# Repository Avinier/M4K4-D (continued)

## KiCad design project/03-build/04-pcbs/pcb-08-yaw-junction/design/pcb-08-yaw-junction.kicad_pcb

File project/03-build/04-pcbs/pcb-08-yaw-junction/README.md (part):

# PCB-08 — Yaw junction

Stationary end of the clock spring: body-side power and signal connectors to the cassette FFCs (`J8-6`, `J8-7`).

**[D-093](../../decisions.md#d-093) scope (2026-11-06).** PCB-02 and PCB-03 are bought modules now, so the `W23a` (`J8-3`) and `W23b` (`J8-5`) permit and status cables and the D-082 `ARM_REQ` conductor are gone. PCB-08 **gains the yaw servo plug** that was PCB-03 `J3-5`: Feetech 5264-3P, 1 GND, 2 `+11V1_YAW` (from the bought yaw buck-boost, 11.1 V), 3 `SERVO_DATA` (from C2 through W43). It keeps `J8-1` (head power from the bought modules), `J8-4` (RS-422 head link, J9-1 order per D-092) and the `J8-6`/`J8-7` cassette FFCs. Reassign the freed W43 conductors at design.

| | |
|---|---|
| Register | [04-pcbs board register](../README.md#board-register) |
| Project BOM | CH-083 in [BOM.csv](../../BOM.csv) |
| Location | Body, under the yaw adapter plate |
| Specification | [05-harness](../../05-harness/README.md)<br>[D-039](../../decisions.md#d-039), [D-044](../../decisions.md#d-044) |
| CAD placeholder | `_yaw_junction_board()` in [`body_v1_model.py`](../../02-body/v1/cad/body_v1_model.py) |
| CAD labels | `YAW_JUNCTION_PCB08` |
| Final CAD | `Custom PCBs › PCB-08 yaw junction` in [makad-v1.step.py](../../final/v1/cad/makad-v1.step.py) |

## Stages

See [workflow.md](../workflow.md) for what each stage involves and when it is done.

| Stage | Status | Revision / evidence | Date |
|---|---|---|---|
| 1. Design | **Rev A draft complete**: routed, populated fit 18/18, fold predicted 10/10, [fab/revA](fab/revA/README.md) written (**do not order**) | [design/](design/): Nightly ERC 0/0, netlist audit 14/14 on 51 pins, parity DRC 0 violations / 0 unconnected / 0 parity; [STEP](cad/pcb-08-yaw-junction-revA.step) with detailed connector models | 2026-11-09 |
| 2. Procure | Waits for the PCB-12/14 designs (D-064) and the bench gates in [fab/revA](fab/revA/README.md#before-ordering) | Do not order fab/revA yet | — |
| 3. Integrate | Rev A STEP installed in final CAD (`pcb_integration.py`, integration PASS) | Physical acceptance open | 2026-11-10 |

## Design inputs (2026-11-09; preliminary)

The board is a passive stator junction: it distributes three head power/return pairs from `J8-1` to `J8-6`, passes the two RS-422 pairs from `J8-4` through `J8-7`, brings `SERVO_DATA` back from `J8-7` to the body-fixed yaw `J8-8`, and takes the yaw rail/return from `W17` pads to `J8-8`. There is no `ARM_REQ`, permit chain, or old `J8-3`/`J8-5` header. No 11.1 V yaw power goes onto either FFC. See [D-093](../../decisions.md#d-093), [D-092](../../decisions.md#d-092), the [harness pinouts](../../05-harness/README.md#5-pinouts-and-polarity), and the [servo link contract](../feetech-link-contract.md).

| Interface | Fixed electrical contract | Board action |
|---|---|---|
| `J8-1`, Micro-Fit 3.0 2×3, right-angle, mating −X | 1 `+6V3_HEAD_PR` (D-100), 2 `+5V_C2`, 3 `+5V_DISPLAY`, 4 `GND_HEAD`, 5 `GND_C2`, 6 `GND_DISPLAY` | Preserve the three supply/return pairs; do not use a signal return as a power-current shortcut |
| `J8-4`, GH6 | 1 GND, 2 `C0TX+`, 3 `C0TX−`, 4 `C2TX−`, 5 `C2TX+`, 6 spare | Pass both differential pairs to `J8-7` in the same polarity. Keep pin 6 isolated unless a later interface decision assigns it |
| `J8-6`, 22-way power FFC | Pitch/roll 7 positive + 7 return; C2 2 + 2; display 2 + 2 | A conductor may carry no more than its connector and cable rating; pair the same rail only at the board ends |
| `J8-7`, 22-way sideband FFC | RS-422 pairs, signal reference and `SERVO_DATA`; former permit/status nets removed | Allocate explicit grounds beside signal groups; leave unused contacts unconnected and labelled, never silently repurpose them as power |
| `W17` → `J8-8`, yaw servo | `J8-8`: 1 GND, 2 `+11V1_YAW`, 3 `SERVO_DATA` | W17 enters on rated pads/strain relief; check the received servo cable by cavity number before energizing |

**FFC maps ([D-100](../../decisions.md#d-100), pending cable orientation).** Number by the *connector's marked contact number* at PCB-08, then measure whether each cable arrives straight or mirrored at PCB-14. PCB-14 remains 1:1; its physical orientation must not reverse these names. `J8-6`: 1–7 `+6V3_HEAD_PR`, 8–14 `GND_HEAD`, 15–16 `+5V_C2`, 17–18 `GND_C2`, 19–20 `+5V_DISPLAY`, 21–22 `GND_DISPLAY`. `J8-7` is **signal-only**: 1 GND reference, 2 `C0TX+`, 3 `C0TX−`, 4 GND reference, 5 `C2TX−`, 6 `C2TX+`, 7 GND reference, 8 `SERVO_DATA`, 9 GND reference, 10–22 isolated and labelled. The 13/13 option (10–15 `GND_HEAD`, 16–21 head positive on `J8-7`) is the recorded fallback only if the measured FFC or N2 fails the 7/7 map. The GND reference source and head-end return must be resolved with PCB-12; the separate `J8-1` returns must not be unintentionally joined on the stator.

**Signal ground (builder, 2026-11-09; [D-100](../../decisions.md#d-100) amendment).** PCB-08 has one signal ground net, **`GND_SIG`**: `J8-4` pin 1 (C0 link GND over W24), `J8-7` pins 1/4/7/9, and `J8-8` pin 1 with the W17 yaw return. `SERVO_DATA` is a single-ended 1 Mbps half-duplex line from C2 to the yaw servo, so its return must run beside it on the `J8-7` references and meet the servo's own ground at `J8-8`. `GND_HEAD` (`J8-1` pin 4 → `J8-6` 8–14), `GND_C2` and `GND_DISPLAY` stay separate on PCB-08, each paired with its supply back to the star. PCB-12 bonds `GND_SIG` to C2 logic ground near the RS-422 receiver and servo-bus driver; all head grounds join there. **Accepted loop:** Pi → M4 → star → M3 → W17 → PCB-08 → W24 → PCB-09 → Pi. Most yaw stall current returns directly on W17, but some can share the W24 GND (GH, 1 A contacts); RS-422 is differential. **Bench:** W24 GND current at yaw stall, C0↔C2 common-mode voltage under simultaneous servo/display load, and `SERVO_DATA` edges at `J8-8`. **Fallback:** a series ferrite or low-value resistor between `J8-4` pin 1 and `GND_SIG` (leave a footprint at layout).

**Current and voltage-drop screen (`E`, not a measured cable).** FH34SRJ is rated 0.5 A/contact. Seven equal-sharing contacts have a nominal 3.5 A sum against the 2.8 A head allowance; two have 1.0 A for each C2/display branch. For voltage, assume copper resistivity 0.01724 Ω·mm²/m, conductor width 0.3 mm, total FFC length 0.3 m, four ZIF contact interfaces in series, and the FH34SRJ specification's 0.1 Ω maximum per contact **including 8 mm of FFC bulk**. Adding that limit to the full cable length double-counts a small portion, so it is deliberately conservative. The table is reproduced by [`head_power_drop.py`](head_power_drop.py). It shows a 0.035 mm conductor and a thinner 0.027 mm sensitivity case. The latter matches the nominal copper thickness in Raspberry Pi's **standard-mini display cable drawing**, but neither case is a claim about the actual BO-050 mini-mini or power FFC. [FH34SRJ specification](https://www.hirose.com/en/product/p/CL0580-1254-3-99); [Raspberry Pi cable drawing](https://pip-assets.raspberrypi.com/categories/903-flexible-printed-circuit-fpc-cable-for-display-and-camera/documents/RP-008145-DS-1-mini-display-cable-200mm-reference-drawing.pdf).

| Copper thickness | Head positive/return conductors | Calculated loop Ω | Drop at 2.8 A | Terminal at 5.5 V | Terminal at 6.0 V | Terminal at 6.3 V |
|---:|---:|---:|---:|---:|---:|---:|
| 0.035 mm | 7 / 7 | 0.255 | 0.714 V | 4.79 V | 5.29 V | 5.59 V |
| 0.027 mm | 7 / 7 | 0.297 | 0.831 V | 4.67 V | 5.17 V | 5.47 V |
| 0.035 mm | 13 / 13 | 0.137 | 0.384 V | 5.12 V | 5.62 V | 5.92 V |
| 0.027 mm | 13 / 13 | 0.160 | 0.447 V | 5.05 V | 5.55 V | 5.85 V |

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
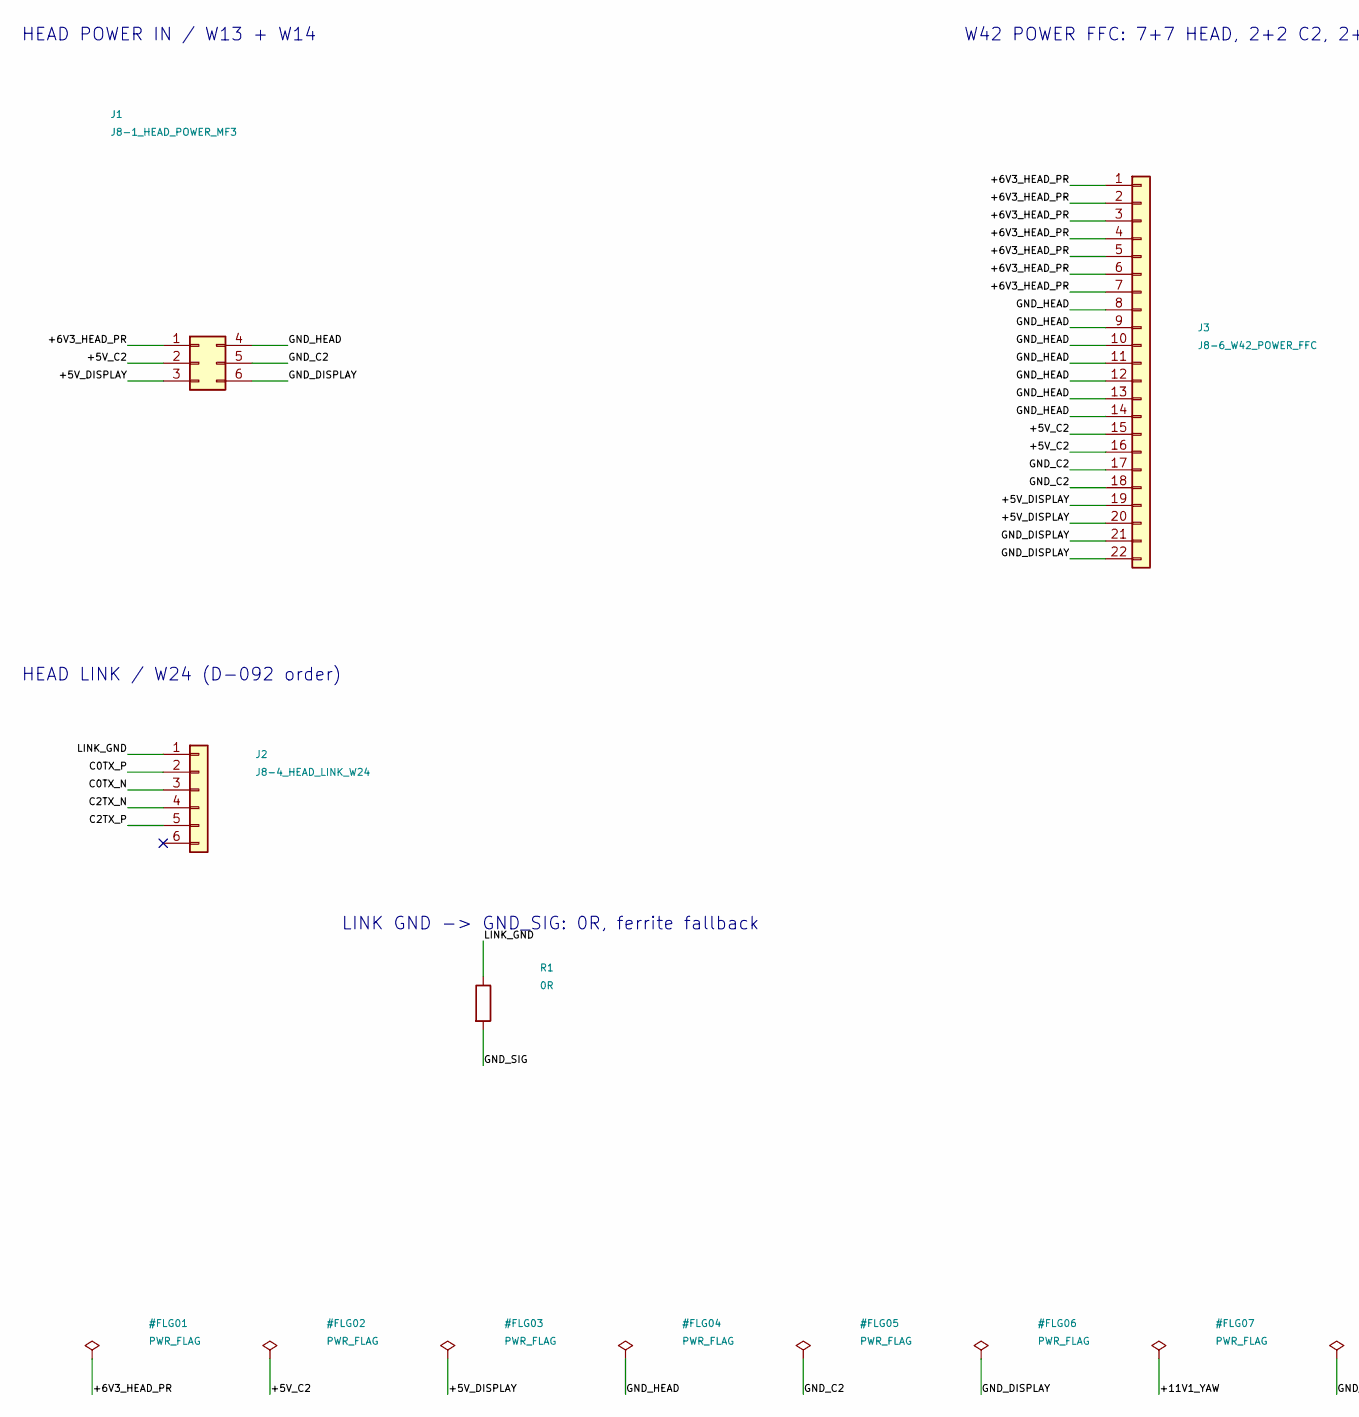
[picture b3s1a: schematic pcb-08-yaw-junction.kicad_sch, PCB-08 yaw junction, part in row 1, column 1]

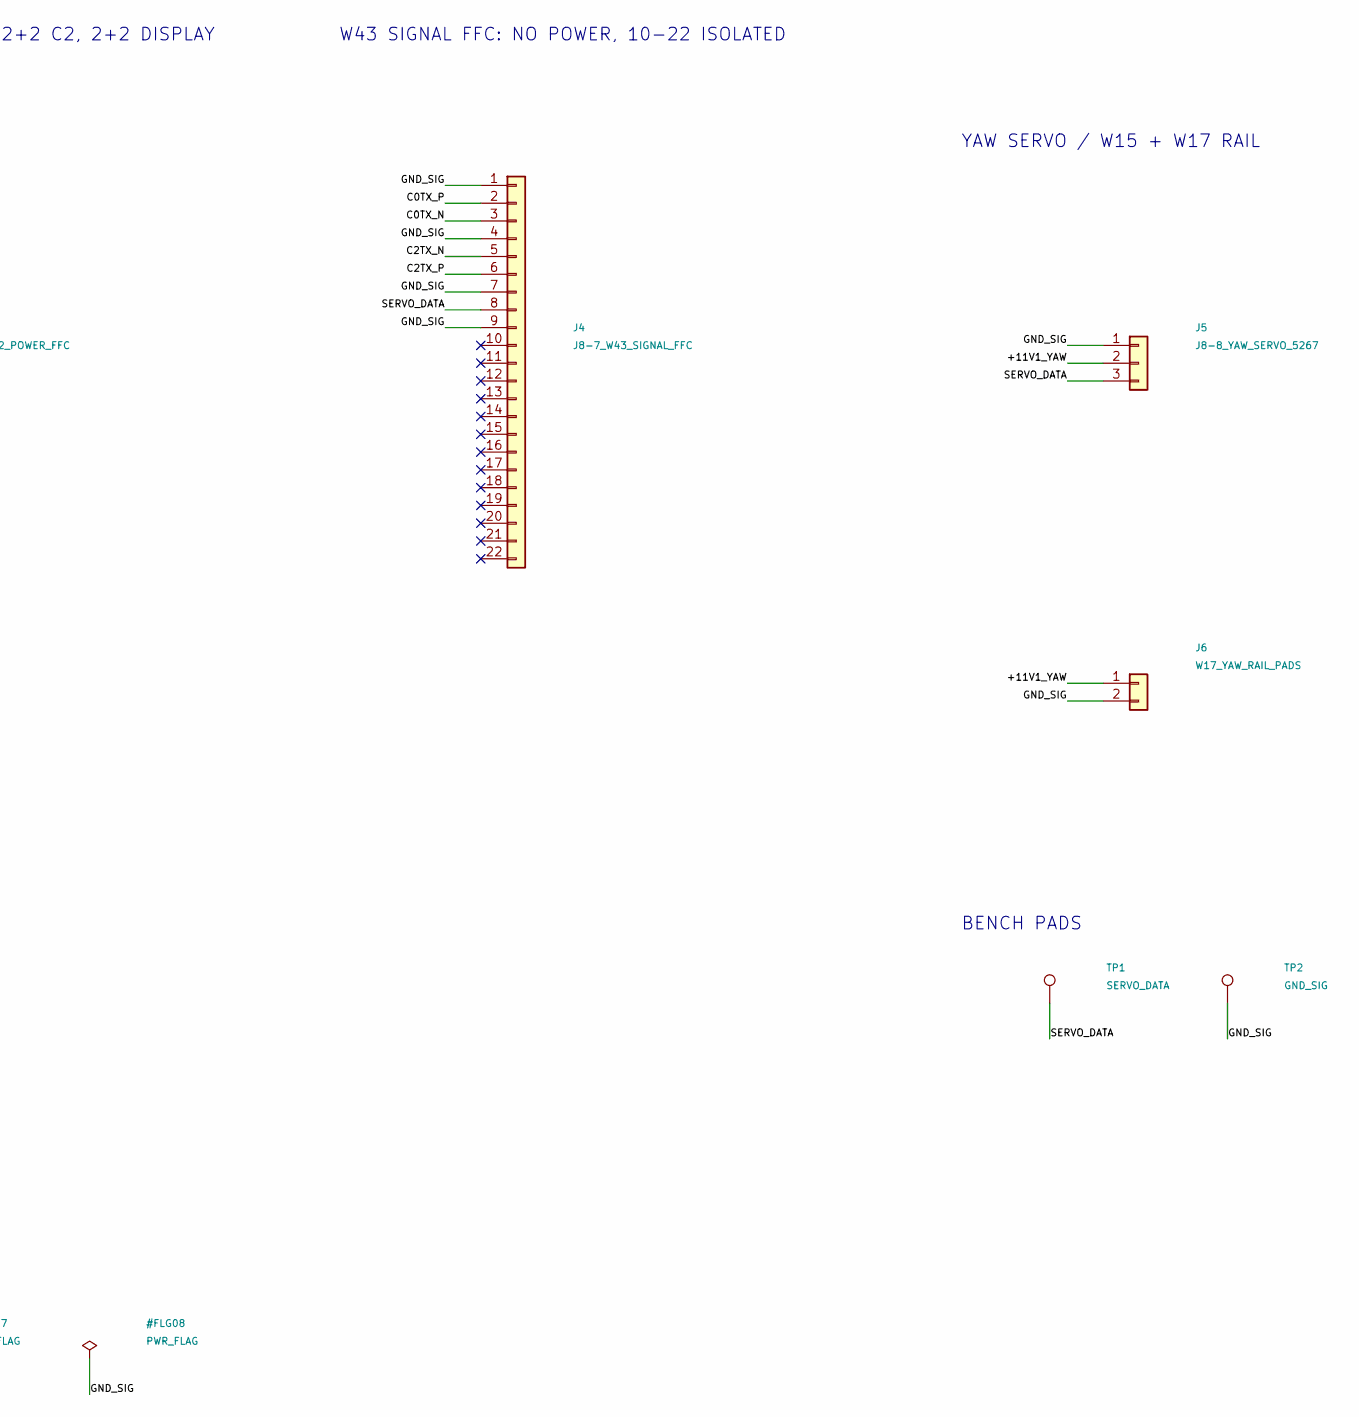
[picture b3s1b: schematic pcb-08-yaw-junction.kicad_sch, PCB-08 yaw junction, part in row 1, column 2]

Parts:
J1: J8-1_HEAD_POWER_MF3; Molex_Micro-Fit_3.0_43045-0621_2x03-1MP_P3.00mm_Horizontal
J2: J8-4_HEAD_LINK_W24; JST_GH_BM06B-GHS-TBT_1x06-1MP_P1.25mm_Vertical
J3: J8-6_W42_POWER_FFC; Hirose_FH34SRJ-22S-0.5SH_1x22_P0.50mm
J4: J8-7_W43_SIGNAL_FFC; Hirose_FH34SRJ-22S-0.5SH_1x22_P0.50mm
J5: J8-8_YAW_SERVO_5267; Molex_SPOX_5267-03A_1x03_P2.50mm_Vertical
J6: W17_YAW_RAIL_PADS; SolderWire-0.5sqmm_1x02_P4.6mm_D0.9mm_OD2.1mm
R1: 0R; R_0805_2012Metric
TP1: SERVO_DATA; TestPoint_Pad_D1.0mm
TP2: GND_SIG; TestPoint_Pad_D1.0mm

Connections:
/+5V_C2: J1.2, J3.15, J3.16
/+5V_DISPLAY: J1.3, J3.19, J3.20
/+6V3_HEAD_PR: J1.1, J3.1, J3.2, J3.3, J3.4, J3.5, J3.6, J3.7
/+11V1_YAW: J5.2, J6.1
/C0TX_N: J2.3, J4.3
/C0TX_P: J2.2, J4.2
/C2TX_N: J2.4, J4.5
/C2TX_P: J2.5, J4.6
/GND_C2: J1.5, J3.17, J3.18
/GND_DISPLAY: J1.6, J3.21, J3.22
/GND_HEAD: J1.4, J3.8, J3.9, J3.10, J3.11, J3.12, J3.13, J3.14
/GND_SIG: J4.1, J4.4, J4.7, J4.9, J5.1, J6.2, R1.2, TP2.1 (1_1)
/LINK_GND: J2.1, R1.1
/SERVO_DATA: J4.8, J5.3, TP1.1 (1_1)

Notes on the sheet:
HEAD POWER IN / W13 + W14
HEAD LINK / W24 (D-092 order)
LINK GND -> GND_SIG: 0R, ferrite fallback
W42 POWER FFC: 7+7 HEAD, 2+2 C2, 2+2 DISPLAY
W43 SIGNAL FFC: NO POWER, 10-22 ISOLATED
YAW SERVO / W15 + W17 RAIL
BENCH PADS

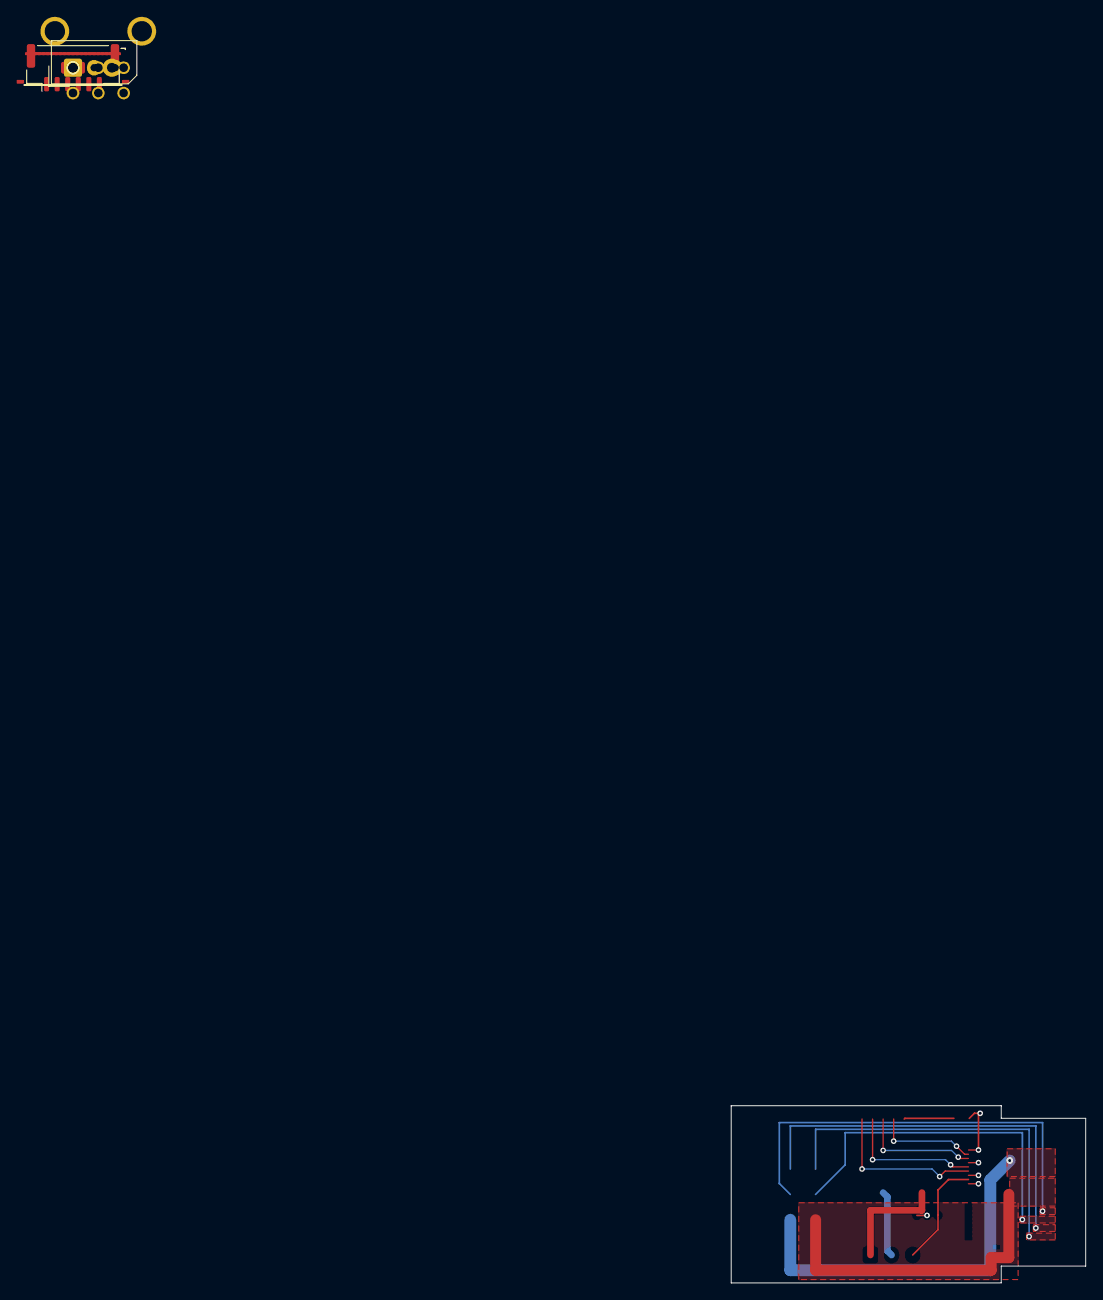
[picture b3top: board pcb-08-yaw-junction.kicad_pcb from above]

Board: 2 copper layers, 42.0 x 21.0 mm, 9 parts (0 on the bottom side), 14 nets.

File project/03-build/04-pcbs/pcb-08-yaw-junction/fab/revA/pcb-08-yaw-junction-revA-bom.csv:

"Comment","Designator","Footprint","Quantity","MPN","Manufacturer","LCSC Part #"
"J8-1_HEAD_POWER_MF3","J1","pcb08:Molex_Micro-Fit_3.0_43045-0621_2x03-1MP_P3.00mm_Horizontal","1","43045-0621","Molex",""
"J8-4_HEAD_LINK_W24","J2","Connector_JST:JST_GH_BM06B-GHS-TBT_1x06-1MP_P1.25mm_Vertical","1","BM06B-GHS-TBT(LF)(SN)(N)","JST",""
"J8-6_W42_POWER_FFC","J3","fh34:Hirose_FH34SRJ-22S-0.5SH_1x22_P0.50mm","1","FH34SRJ-22S-0.5SH(99)","Hirose",""
"J8-7_W43_SIGNAL_FFC","J4","fh34:Hirose_FH34SRJ-22S-0.5SH_1x22_P0.50mm","1","FH34SRJ-22S-0.5SH(99)","Hirose",""
"J8-8_YAW_SERVO_5267","J5","Connector_Molex:Molex_SPOX_5267-03A_1x03_P2.50mm_Vertical","1","22-03-5035 (5267-03A)","Molex",""
"0R","R1","Resistor_SMD:R_0805_2012Metric","1","RC0805JR-070RL","Yageo",""

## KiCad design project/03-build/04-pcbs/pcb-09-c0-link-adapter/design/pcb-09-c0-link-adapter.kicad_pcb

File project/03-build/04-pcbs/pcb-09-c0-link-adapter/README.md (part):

# PCB-09 — C0 link adapter

Pi-header board: 2 × RS-422 (THVD1451), audio pass-through and the enclosure-fan switch `J9-4`. **Rev A designed** ([D-092](../../decisions.md#d-092)): 77 × 22.7 × 1.6 mm, four layers, on the Pi header through a Samtec SSW-120-01-T-D socket and two M2.5 × 11 mm standoffs. **Rev B routed and CAD fitted on `pcb-09-revB`, not released** ([D-098](../../decisions.md#d-098)): 89 × 22.7 × 1.6 mm overall, adding the D-096 button/OFF and INA226 service interface. The #2813, Pi-image and populated bench gates below still apply; do not order either revision yet.

| | |
|---|---|
| Register | [04-pcbs board register](../README.md#board-register) |
| Project BOM | CH-084 in [BOM.csv](../../BOM.csv) |
| Location | Body, on the Pi header |
| Specification | [audiosystem.md §4](../../02-body/v1/research/audiosystem.md#4-audio-functions-on-the-shared-boards)<br>[D-042](../../decisions.md#d-042), [D-073](../../decisions.md#d-073), [D-074](../../decisions.md#d-074), [D-092](../../decisions.md#d-092), [D-098](../../decisions.md#d-098) |
| CAD placeholder | `_c0_link_adapter()` in [`body_v1_model.py`](../../02-body/v1/cad/body_v1_model.py) |
| CAD labels | `C0_LINK_ADAPTER_PCB09` |
| Final CAD | `Custom PCBs › PCB-09 C0 link adapter` in [makad-v1.step.py](../../final/v1/cad/makad-v1.step.py): rev-B KiCad STEP, standoffs, screws and five mated plugs ([pcb_integration.py](../../final/v1/cad/pcb_integration.py)); rev-B fit 8/8, mount 7/7 and integration PASS |

## Stages

See [workflow.md](../workflow.md) for what each stage involves and when it is done.

| Stage | Status | Revision / evidence | Date |
|---|---|---|---|
| 1. Design | **Rev B routed and CAD fitted; electrical release gates open** ([D-098](../../decisions.md#d-098)) | ERC 0; exported netlist audit PASS for 118 connected pins; Nightly DRC 0 violations / 0 unconnected / 0 parity; rev-B fit 8/8, mount 7/7, final integration PASS. `fab/revB` is a draft output, not an order release. | 2026-11-08 |
| 2. Procure | Waits for rev B and the design batch ([D-064](../../decisions.md#d-064)) | Do not order fab/revA | — |
| 3. Integrate | Rev B CAD replacement complete; physical acceptance open | [pcb_integration.py](../../final/v1/cad/pcb_integration.py), `check_pcb_integration.py`; J6 lead route to rear bay passes a 3 mm CAD reserve with 0.2 mm margin. J6 must be mated before tray installation. | 2026-11-08 |

### Rev B input — D-098

Preserve the rev A functions, socket, mounting and existing connector pinouts. Add accessible service access to **GPIO12 / header 32** for the qualified 0–3.3 V button-sense signal and **GPIO13 / header 33** for the M1 OFF command. The [D-098 amendment](../../decisions.md#d-098) assigns the INA226 to a local `i2c-gpio` bus: draft SDA on GPIO16 / header 36 and SCL on GPIO26 / header 37, plus Pi 3.3 V and GND. Physical pins 3/5 keep their rev A I²C1 routes to TP1/TP2 only. TP5 and TP1/TP2 are 1 mm probe pads, not harness terminations.

Rev B selects J6 as a top-entry GH6 on the +X extension. CAD checks its mated plug, a 3 mm lead corridor toward the rear buffer, and pre-mated tray insertion; add strain relief and pull-test the lead on the populated build. Keep the M1 ON pack-voltage node off this board: GPIO12 receives only the output of the measured high-impedance interface, with no back-power path into an unpowered Pi. Check GPIO13's inactive state through Pi reset, boot and halt, and any M1-to-GPIO13 injection with Pi power absent, before connecting OFF. ERC/DRC, six-net continuity/no-short checks and N1 are release gates. D-096's separate electrical HOLD still applies.

### Rev B routing study — 2026-11-08

The [rev B schematic](design/pcb-09-c0-link-adapter.kicad_sch) adds J6 (GH6: **1 3V3, 2 SDA, 3 SCL, 4 GND, 5 BTN_SENSE, 6 PWR_OFF**), R7 10 kΩ button pull-up to Pi 3V3, R8 2.2 kΩ button series, C5 100 nF optional/DNP, R9 1 kΩ OFF series, R10 100 kΩ OFF pull-down, and R11/R12 4.7 kΩ pull-ups for the software I²C bus. GPIO12/13 terminate at header pins 32/33; draft SDA/SCL terminate at pins 36/37. The connector nets are on the 3.3 V side; pack voltage and load current are absent. The received #2813 measurements still gate final values and buffer choice.

| Header pin | Rev B schematic net | Destination | Layout status |
|---|---|---|---|
| 3 / GPIO2 | I2C1_SDA | TP1 only, unchanged from rev A | Rev A route retained in rev B |
| 5 / GPIO3 | I2C1_SCL | TP2 only, unchanged from rev A | Rev A route retained in rev B |
| 32 / GPIO12 | BTN_GPIO12 | R8 → BTN_SENSE at J6.5 | Routed in rev B; DRC 0/0/0 |
| 33 / GPIO13 | OFF_GPIO13 | R9 → PWR_OFF at J6.6 | Routed in rev B; DRC 0/0/0 |
| 36 / GPIO16 | I2C_GPIO_SDA | R11 pull-up and J6.2 | Routed in rev B; DRC 0/0/0 |
| 37 / GPIO26 | I2C_GPIO_SCL | R12 pull-up and J6.3 | Routed in rev B; DRC 0/0/0 |

The draft rev B allocation has **15 functional GPIO** (rev A's 11 plus GPIO12/13/16/26) and keeps GPIO2/3 reserved for I²C1 service pads. Layout and CAD fit validate GPIO16/26 and a top-entry GH6 at the +X extension; electrical acceptance is pending.

An exploratory GH6 placement needed an extension at the bay's +X edge: the existing F.Cu courtyards occupy the top of the original bay. A geometric core-only probe of world X 66…78, Y 22.5…39, Z 106.25…108.25 found no intersecting robot solid. That probe did **not** validate the mated plug, cable exit, insertion sweep, mount or full board. Growing the +Y edge instead intersected the existing J9-1 mated plug and its reserve.

The manually routed exploratory I²C1 board failed Nightly DRC: **29 violations, 2 unconnected and 0 parity** ([study report](design/revB-routing-study-drc.json)). The SDA F.Cu L path crossed LRCLK near header pin 35; the proposed layer change landed on the existing 5 V via. The SCL B.Cu U path crossed BASE_TX and approached a ground socket pad. The GPIO12/13 In1 paths isolated ground socket pads 30/34; J6's +X placement also conflicted with nearby vias. D-098 therefore switches the INA226 to local GPIO I²C and forbids new In1 tracks. This report is historical evidence from the rejected route.

The amended rev B layout uses local rev A escape reroutes near header pins 32–38, preserves every rev A net and connector pinout, adds no signal track to In1, and passes Nightly DRC 0/0/0. The +X extension ends at world X 78 and steps its +Y edge back to Y 38.9 to clear the body frame. The rev B STEP passes `check_pcb09_fit.py` 8/8, `check_pcb09_mount.py` 7/7, and `check_pcb_integration.py` PASS. `fab/revB/` was exported only after that CAD fit and remains a draft until the bench gates close.

Current evidence: [DRC/parity](design/layout-drc.json), [rev B board STEP](cad/pcb-09-c0-link-adapter-revB.step), [fit report](../../final/v1/cad/check_pcb09_fit-revB-report.json), [mount report](../../final/v1/cad/check_pcb09_mount-revB-report.json), [final STEP integration report](../../final/v1/cad/pcb-integration-report.json), and [draft fabrication outputs](fab/revB/README.md). C5 is DNP and omitted from the assembly BOM/CPL. J6's plug must be mated before the tray slide; its 3 mm lead reserve clears to the rear buffer volume with 0.2 mm CAD margin.

## Inputs

Header audit started 2026-10-31. The electrical interface below is the **builder-agreed allocation baseline v0.2** ([D-073](../../decisions.md#d-073)); CR-02 and boot-safe audit closure remain open. The D-074 strip outline and all 40 socket pad positions have since been checked, and a review schematic and placement exist below. Socket selection, installed height, retention and populated fit were the remaining lesson-1 gaps; they are closed in the [input freeze](#input-freeze--2026-11-06-d-092) (D-092).

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
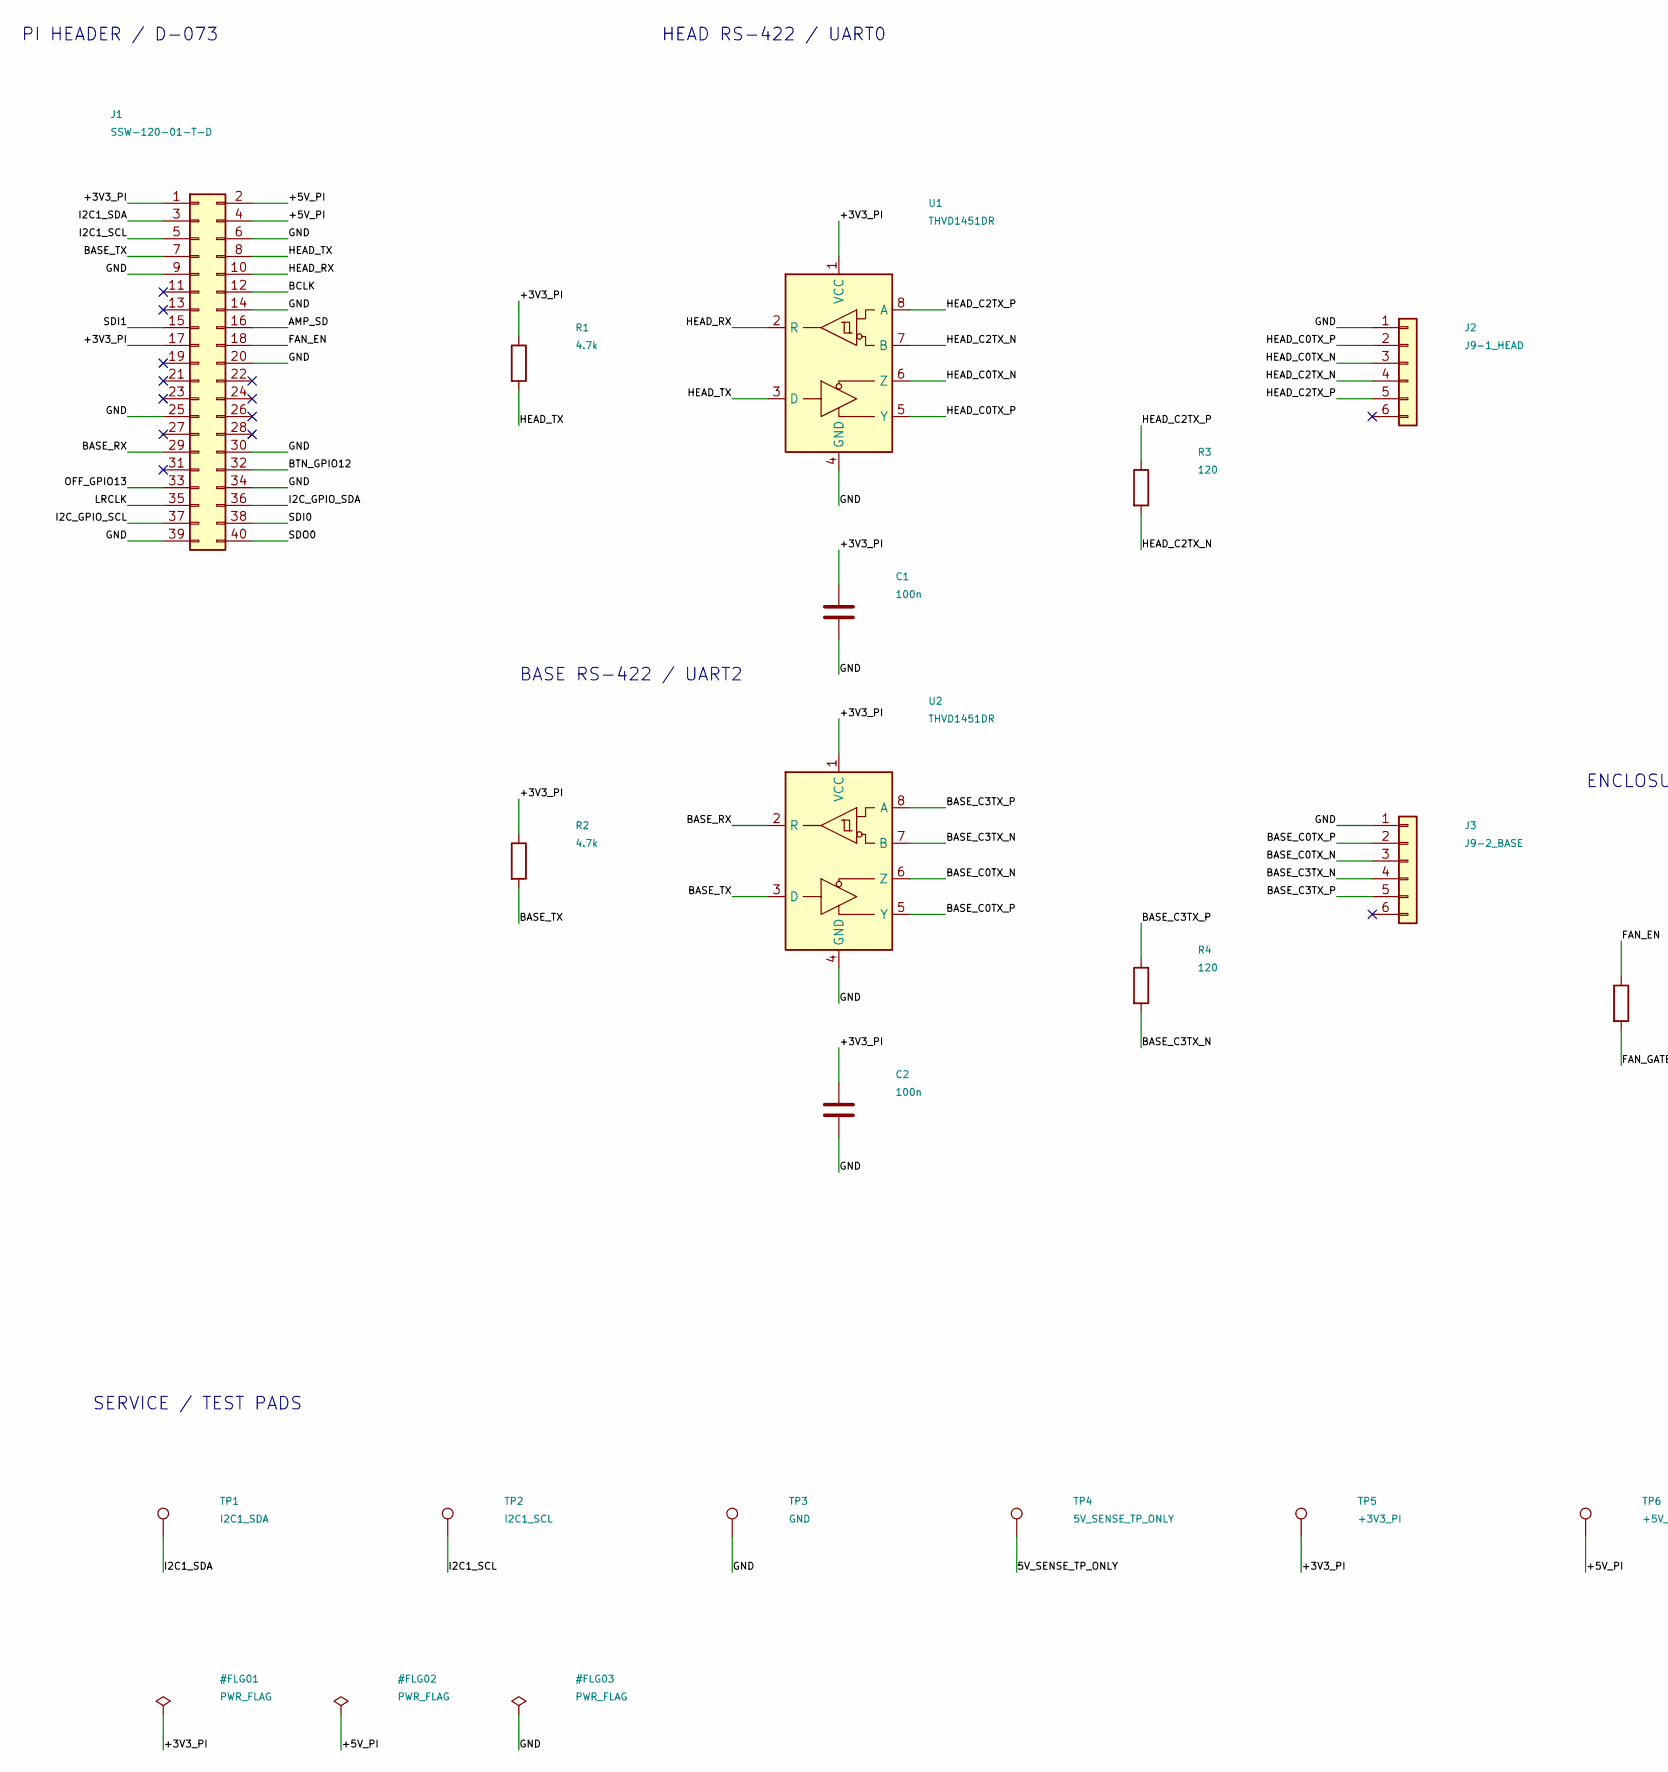
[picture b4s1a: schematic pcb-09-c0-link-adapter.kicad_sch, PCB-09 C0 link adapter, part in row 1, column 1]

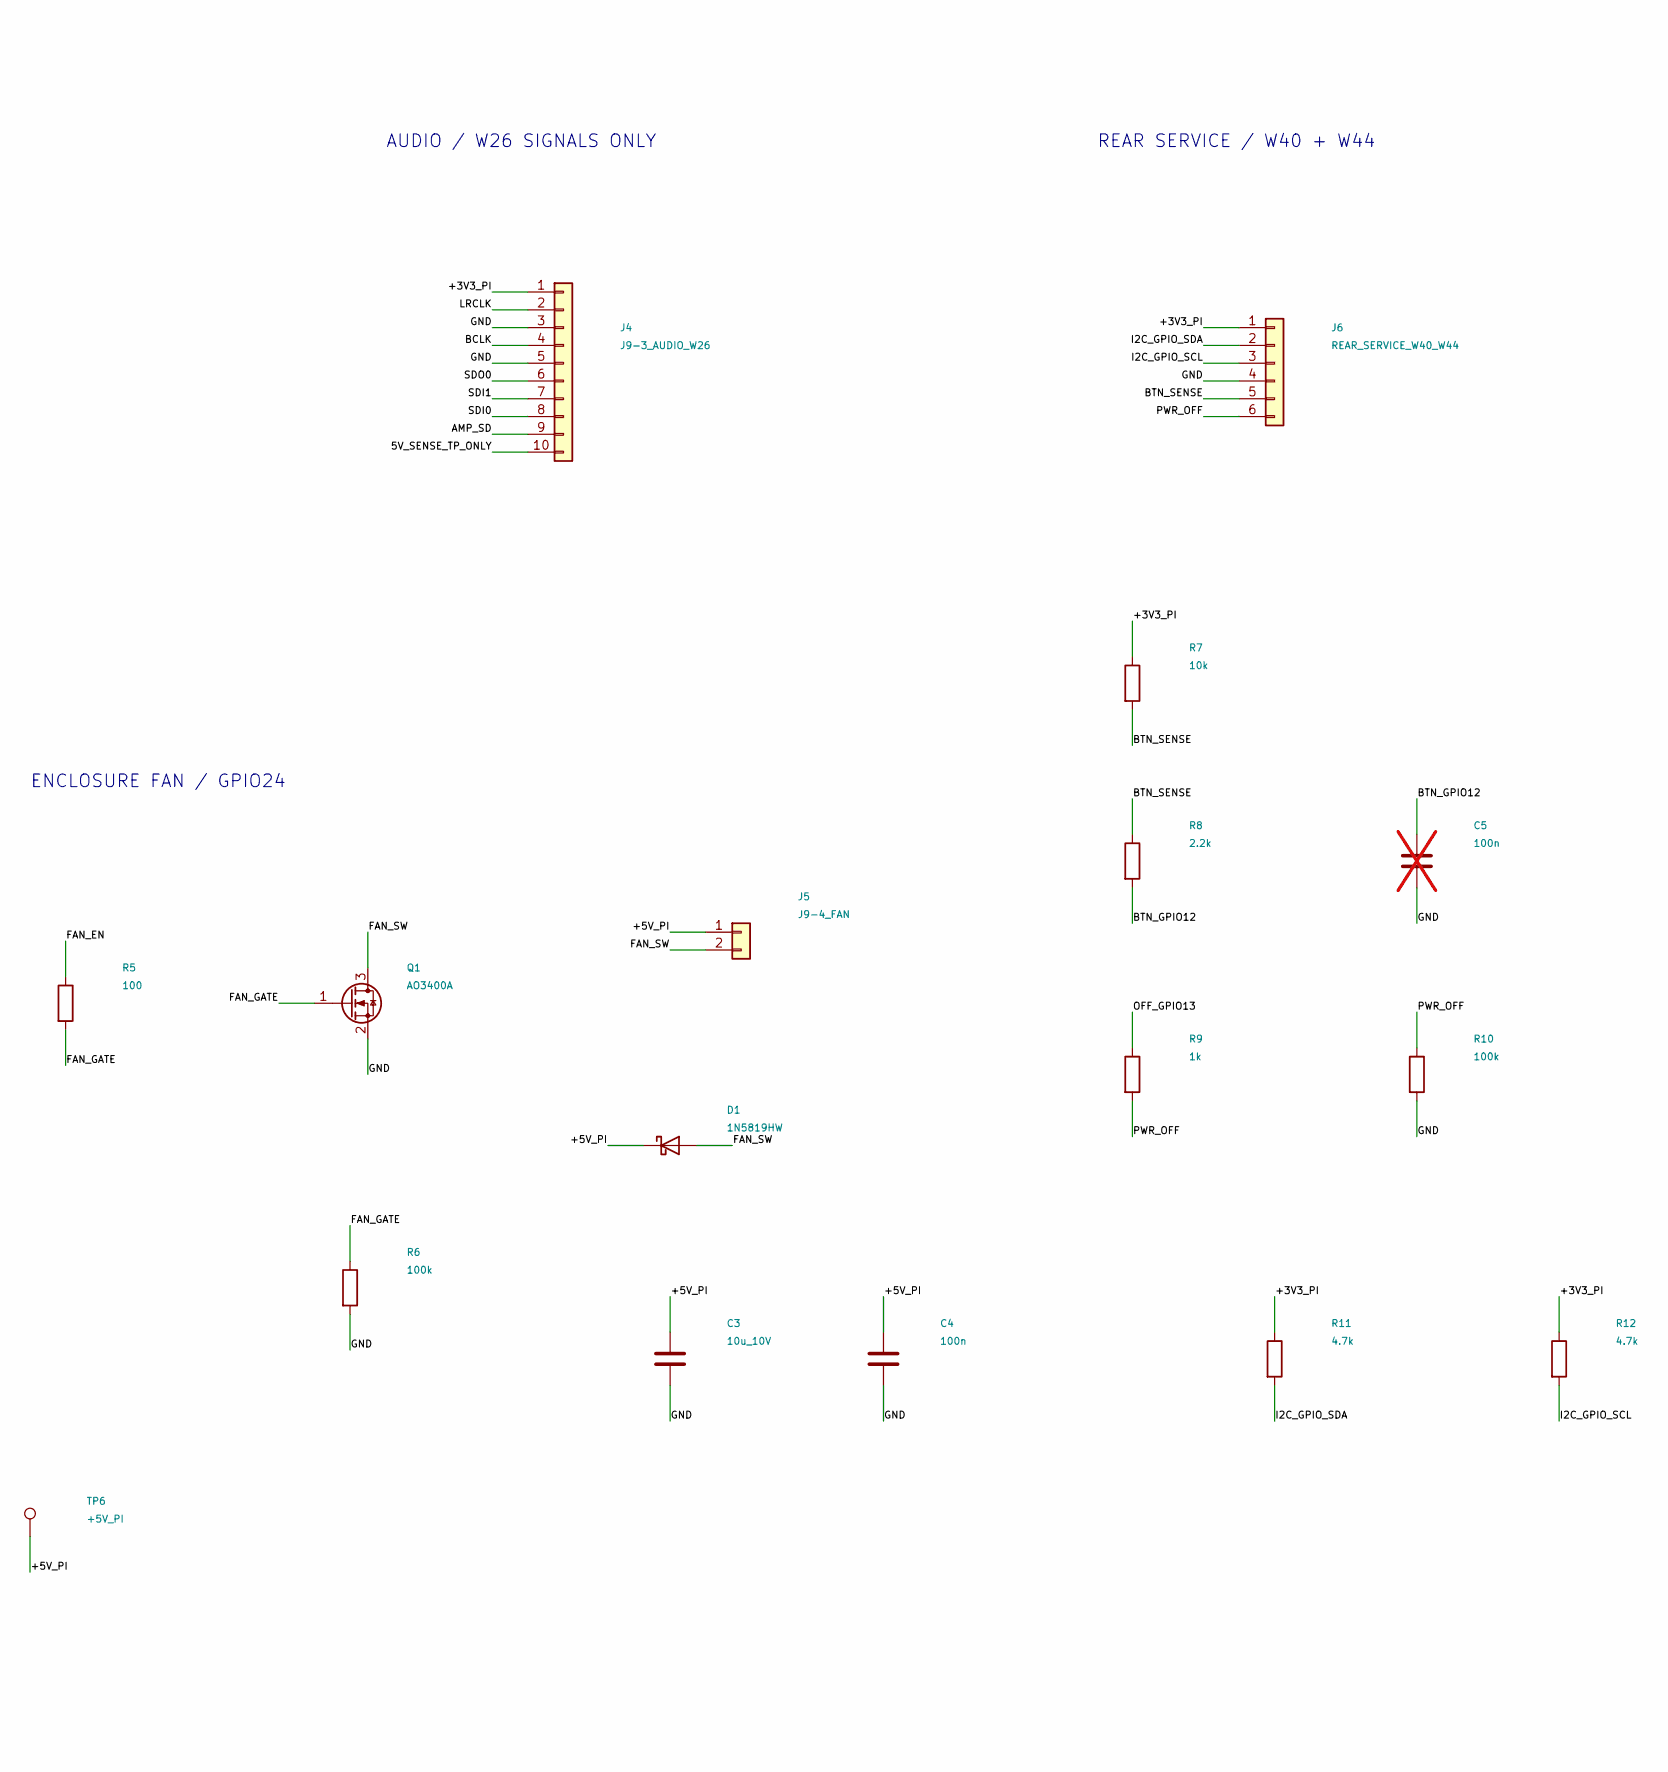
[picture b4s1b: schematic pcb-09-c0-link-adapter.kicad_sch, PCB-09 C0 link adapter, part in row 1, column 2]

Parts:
C1, C2, C4: 100n; C_0603_1608Metric
C3: 10u_10V; C_0805_2012Metric
C5: 100n; C_0603_1608Metric; not fitted
D1: 1N5819HW; D_SOD-123
J1: SSW-120-01-T-D; PinSocket_2x20_P2.54mm_Vertical
J2: J9-1_HEAD; JST_GH_SM06B-GHS-TB_1x06-1MP_P1.25mm_Horizontal
J3: J9-2_BASE; JST_GH_BM06B-GHS-TBT_1x06-1MP_P1.25mm_Vertical
J4: J9-3_AUDIO_W26; JST_GH_BM10B-GHS-TBT_1x10-1MP_P1.25mm_Vertical
J5: J9-4_FAN; JST_GH_BM02B-GHS-TBT_1x02-1MP_P1.25mm_Vertical
J6: REAR_SERVICE_W40_W44; JST_GH_BM06B-GHS-TBT_1x06-1MP_P1.25mm_Vertical
Q1: AO3400A; SOT-23
R1, R2, R11, R12: 4.7k; R_0603_1608Metric
R3, R4: 120; R_0603_1608Metric
R5: 100; R_0603_1608Metric
R6, R10: 100k; R_0603_1608Metric
R7: 10k; R_0603_1608Metric
R8: 2.2k; R_0603_1608Metric
R9: 1k; R_0603_1608Metric
TP1: I2C1_SDA; TestPoint_Pad_D1.0mm
TP2: I2C1_SCL; TestPoint_Pad_D1.0mm
TP3: GND; TestPoint_Pad_D1.0mm
TP4: 5V_SENSE_TP_ONLY; TestPoint_Pad_D1.0mm
TP5: +3V3_PI; TestPoint_Pad_D1.0mm
TP6: +5V_PI; TestPoint_Pad_D1.0mm
U1, U2: THVD1451DR; SOIC-8_3.9x4.9mm_P1.27mm

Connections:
/5V_SENSE_TP_ONLY: J4.10, TP4.1 (1_1)
/+3V3_PI: C1.1, C2.1, J1.1, J1.17, J4.1, J6.1, R1.1, R2.1, R7.1, R11.1, R12.1, TP5.1 (1_1), U1.1 (VCC), U2.1 (VCC)
/+5V_PI: C3.1, C4.1, D1.1 (K), J1.2, J1.4, J5.1, TP6.1 (1_1)
/AMP_SD: J1.16, J4.9
/BASE_C0TX_N: J3.3, U2.6 (Z)
/BASE_C0TX_P: J3.2, U2.5 (Y)
/BASE_C3TX_N: J3.4, R4.2, U2.7 (B)
/BASE_C3TX_P: J3.5, R4.1, U2.8 (A)
/BASE_RX: J1.29, U2.2 (R)
/BASE_TX: J1.7, R2.2, U2.3 (D)
/BCLK: J1.12, J4.4
/BTN_GPIO12: C5.1, J1.32, R8.2
/BTN_SENSE: J6.5, R7.2, R8.1
/FAN_EN: J1.18, R5.1
/FAN_GATE: Q1.1 (G), R5.2, R6.1
/FAN_SW: D1.2 (A), J5.2, Q1.3 (D)
/GND: C1.2, C2.2, C3.2, C4.2, C5.2, J1.6, J1.9, J1.14, J1.20, J1.25, J1.30, J1.34, J1.39, J2.1, J3.1, J4.3, J4.5, J6.4, Q1.2 (S), R6.2, R10.2, TP3.1 (1_1), U1.4 (GND), U2.4 (GND)
/HEAD_C0TX_N: J2.3, U1.6 (Z)
/HEAD_C0TX_P: J2.2, U1.5 (Y)
/HEAD_C2TX_N: J2.4, R3.2, U1.7 (B)
/HEAD_C2TX_P: J2.5, R3.1, U1.8 (A)
/HEAD_RX: J1.10, U1.2 (R)
/HEAD_TX: J1.8, R1.2, U1.3 (D)
/I2C1_SCL: J1.5, TP2.1 (1_1)
/I2C1_SDA: J1.3, TP1.1 (1_1)
/I2C_GPIO_SCL: J1.37, J6.3, R12.2
/I2C_GPIO_SDA: J1.36, J6.2, R11.2
/LRCLK: J1.35, J4.2
/OFF_GPIO13: J1.33, R9.1
/PWR_OFF: J6.6, R9.2, R10.1
/SDI0: J1.38, J4.8
/SDI1: J1.15, J4.7
/SDO0: J1.40, J4.6

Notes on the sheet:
PI HEADER / D-073
HEAD RS-422 / UART0
BASE RS-422 / UART2
AUDIO / W26 SIGNALS ONLY
ENCLOSURE FAN / GPIO24
REAR SERVICE / W40 + W44
SERVICE / TEST PADS

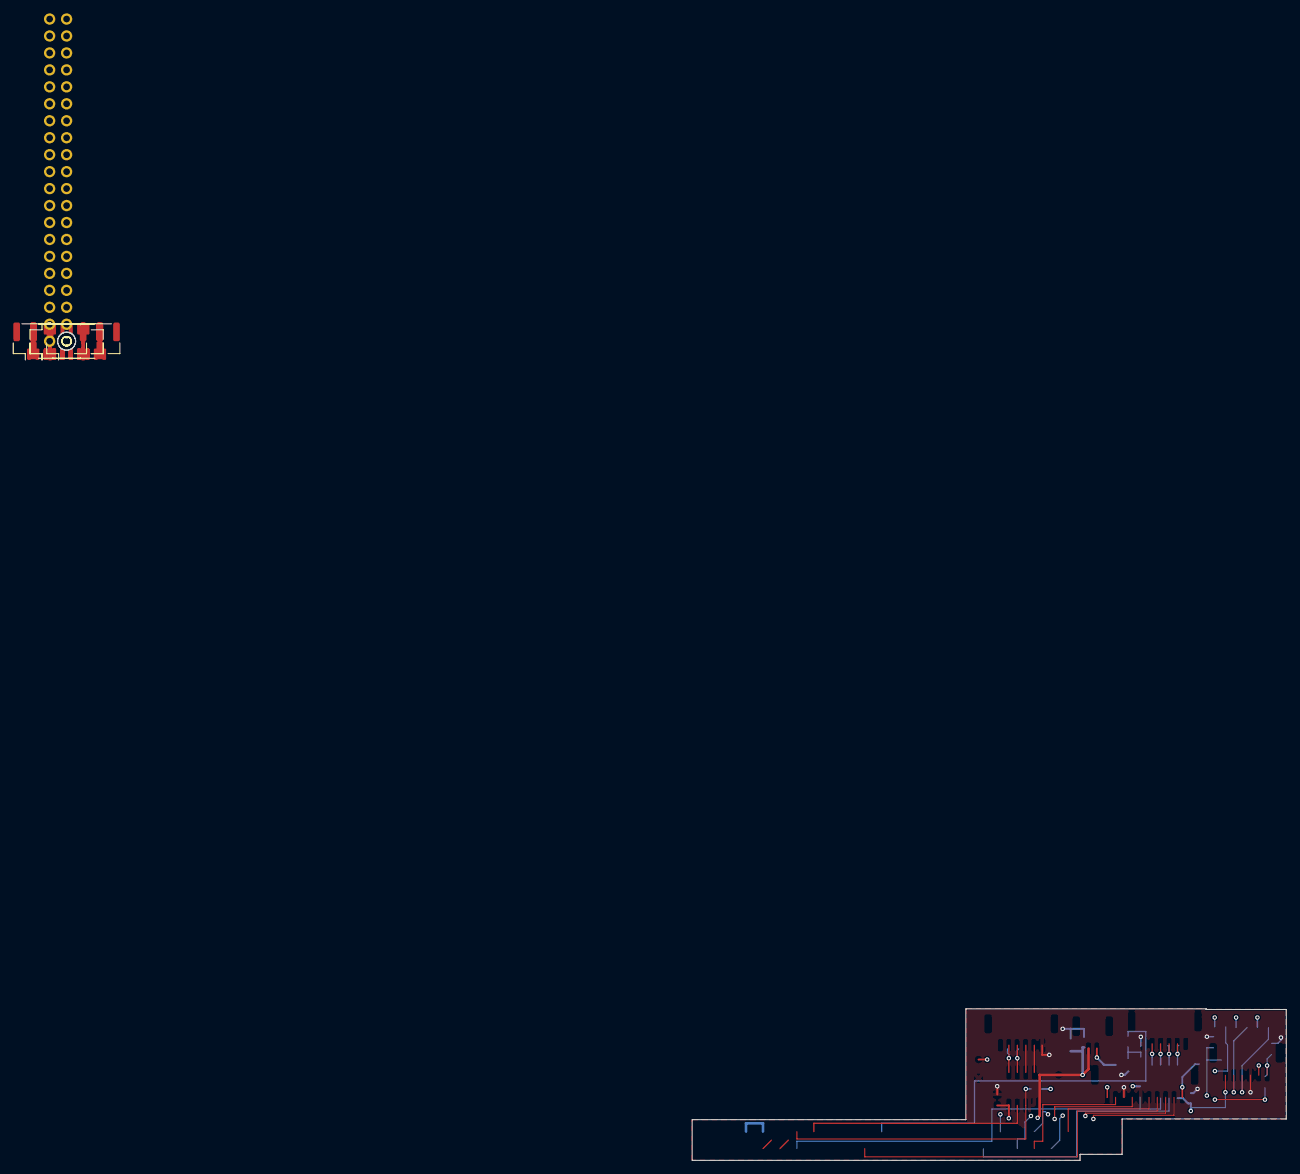
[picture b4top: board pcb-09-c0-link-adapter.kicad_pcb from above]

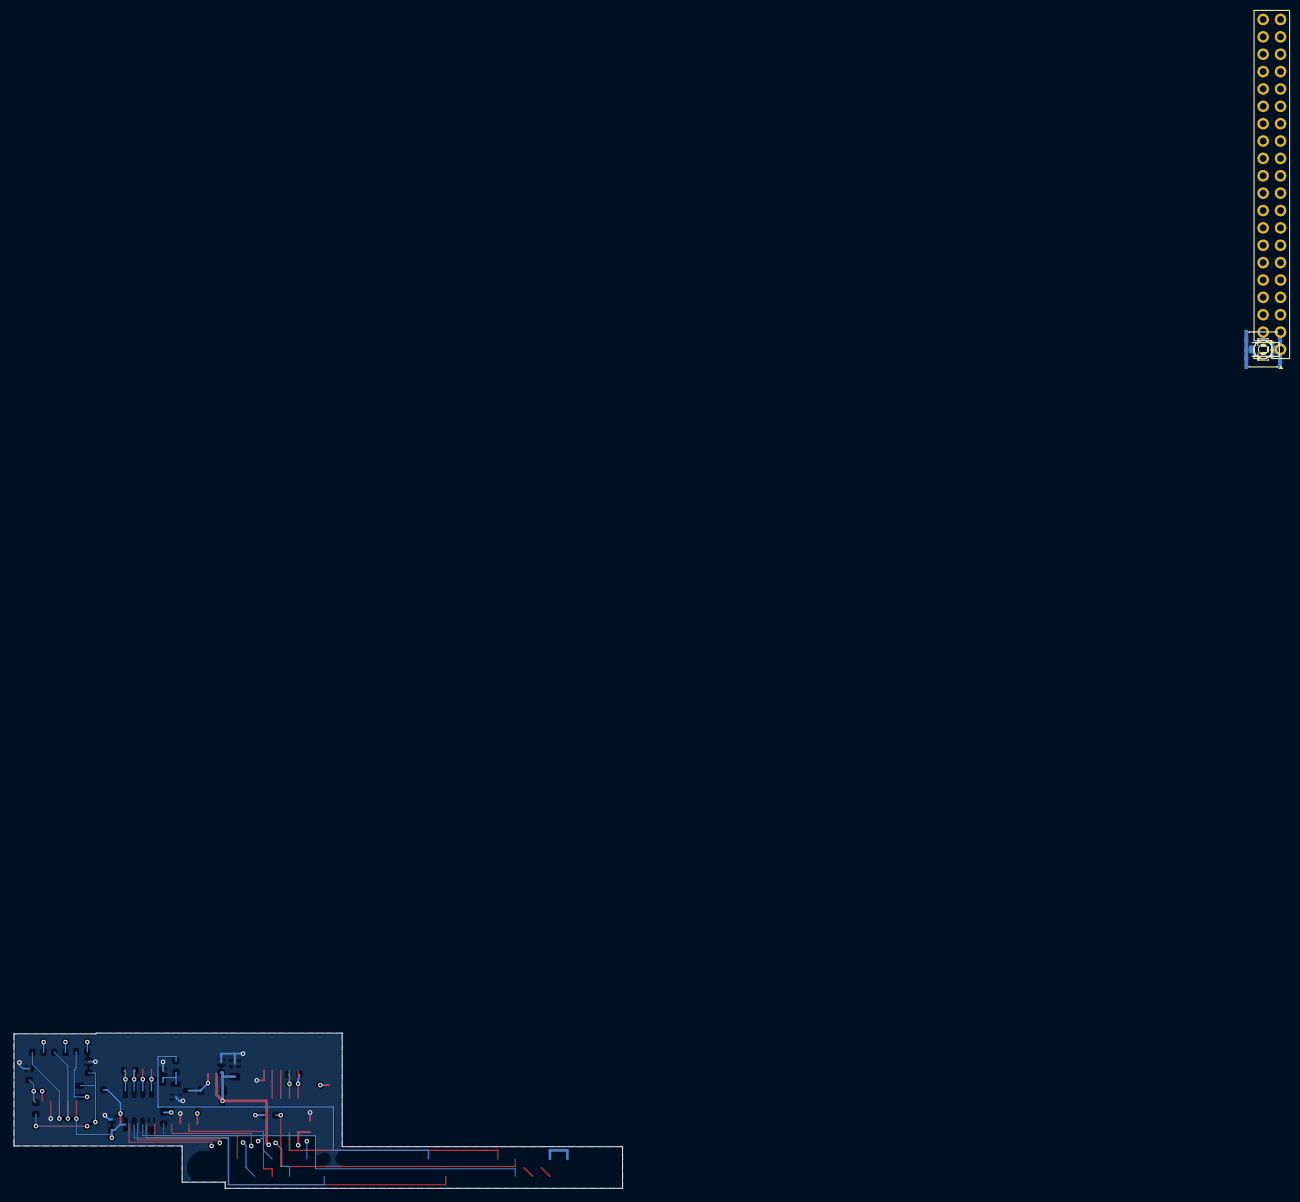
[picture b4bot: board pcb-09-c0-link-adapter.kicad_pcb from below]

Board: 4 copper layers, 89.0 x 22.7 mm, 35 parts (21 on the bottom side), 33 nets.

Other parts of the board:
H1, H2: MountingHole_2.7mm_M2.5

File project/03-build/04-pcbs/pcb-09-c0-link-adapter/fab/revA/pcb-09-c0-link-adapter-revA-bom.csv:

"Comment","Designator","Footprint","Quantity","MPN","Manufacturer","LCSC Part #"
"100n","C1,C2,C4","Capacitor_SMD:C_0603_1608Metric","3","","",""
"10u_10V","C3","Capacitor_SMD:C_0805_2012Metric","1","","",""
"1N5819HW","D1","Diode_SMD:D_SOD-123","1","1N5819HW-7-F","Diodes Inc.",""
"SSW-120-01-T-D","J1","Connector_PinSocket_2.54mm:PinSocket_2x20_P2.54mm_Vertical","1","SSW-120-01-T-D","Samtec",""
"J9-1_HEAD","J2","Connector_JST:JST_GH_SM06B-GHS-TB_1x06-1MP_P1.25mm_Horizontal","1","SM06B-GHS-TB(LF)(SN)","JST",""
"J9-2_BASE","J3","Connector_JST:JST_GH_BM06B-GHS-TBT_1x06-1MP_P1.25mm_Vertical","1","BM06B-GHS-TBT(LF)(SN)(N)","JST",""
"J9-3_AUDIO_W26","J4","Connector_JST:JST_GH_BM10B-GHS-TBT_1x10-1MP_P1.25mm_Vertical","1","BM10B-GHS-TBT(LF)(SN)(N)","JST",""
"J9-4_FAN","J5","Connector_JST:JST_GH_BM02B-GHS-TBT_1x02-1MP_P1.25mm_Vertical","1","BM02B-GHS-TBT(LF)(SN)(N)","JST",""
"AO3400A","Q1","Package_TO_SOT_SMD:SOT-23","1","AO3400A","Alpha & Omega",""
"4.7k","R1,R2","Resistor_SMD:R_0603_1608Metric","2","","",""
"120","R3,R4","Resistor_SMD:R_0603_1608Metric","2","","",""
"100","R5","Resistor_SMD:R_0603_1608Metric","1","","",""
"100k","R6","Resistor_SMD:R_0603_1608Metric","1","","",""
"THVD1451DR","U1,U2","Package_SO:SOIC-8_3.9x4.9mm_P1.27mm","2","THVD1451DR","Texas Instruments",""
